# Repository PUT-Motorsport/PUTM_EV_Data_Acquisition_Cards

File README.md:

# PUTM_EV_Data_Acquisition_Cards
Project to read data from sensors and transmit it via CAN bus.

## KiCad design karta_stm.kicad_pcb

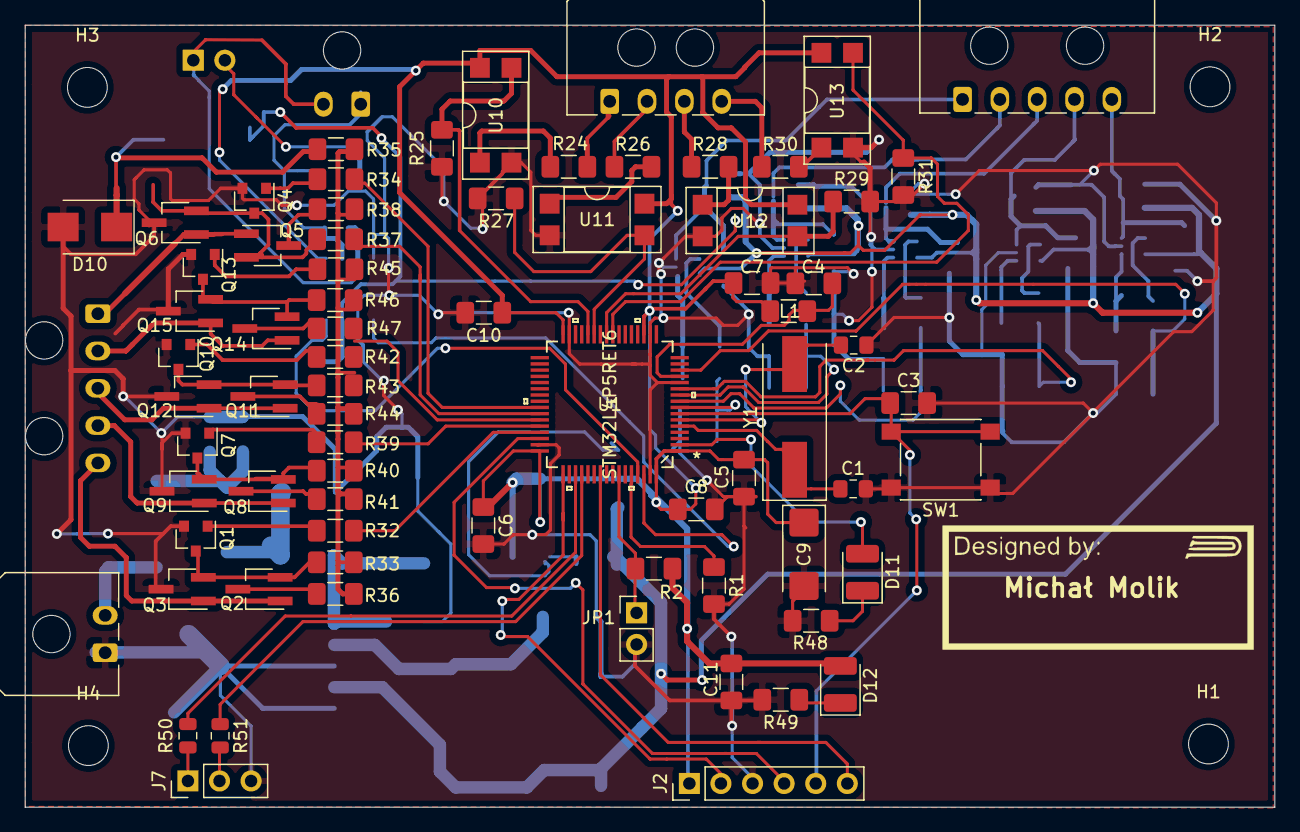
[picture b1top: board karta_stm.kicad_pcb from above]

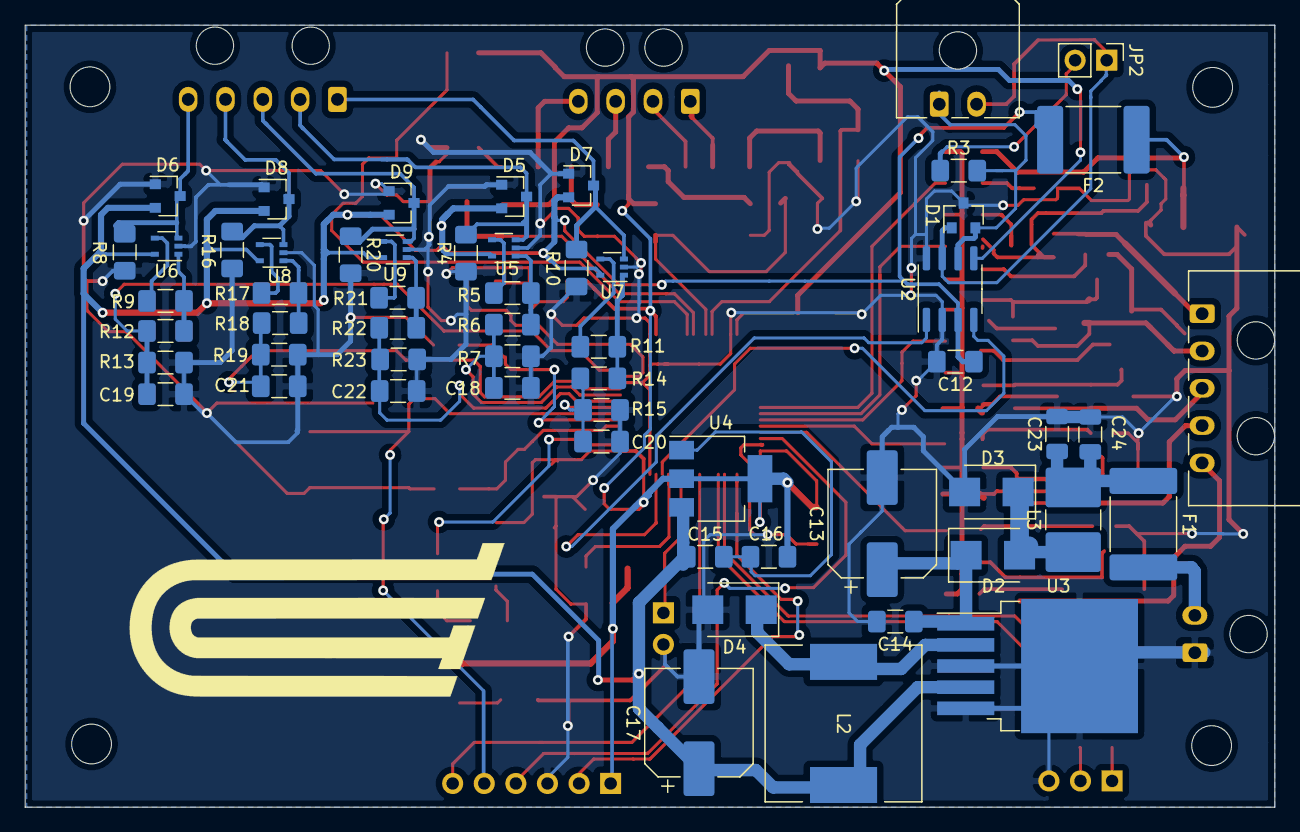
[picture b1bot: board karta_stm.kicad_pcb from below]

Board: 2 copper layers, 100.5 x 62.9 mm, 135 parts (58 on the bottom side), 89 nets.

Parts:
C1, C2: 20pF; C_0805_2012Metric_Pad1.15x1.40mm_HandSolder
C3, C18, C19, C20, C21, C22: 0.1uF; C_1206_3216Metric_Pad1.42x1.75mm_HandSolder
C4, C5, C6, C7, C8, C12, C14, C15, C16: 100nF; C_1206_3216Metric_Pad1.42x1.75mm_HandSolder
C9: 4,7uF; CP_EIA-6032-15_Kemet-U_Pad2.25x2.35mm_HandSolder
C10: 10nF; C_1206_3216Metric_Pad1.42x1.75mm_HandSolder
C11: 1uF; C_1206_3216Metric_Pad1.42x1.75mm_HandSolder
C13: 100uF; CP_Elec_8x10.5
C17: 220uF; CP_Elec_8x10.5
C23, C24: C; C_1206_3216Metric
D1: PESD2CAN,215; SOT-23
D2: SM6T30A; D_SMB
D3: D_Schottky; D_SMB
D4: 1N5824; D_SMB
D5, D6, D7, D8, D9: BAT54S; SOT-23
D10: SM6T6V8A; D_SMB
D11, D12: D; D_1210_3225Metric_Pad1.42x2.65mm_HandSolder
F1: 200mA; Fuse_2920_7451Metric_Pad2.10x5.45mm_HandSolder
F2: 100mA; Fuse_2920_7451Metric_Pad2.10x5.45mm_HandSolder
H1, H2, H3, H4: MountingHole; MountingHole_3.2mm_M3
J1, J4: Conn_01x02_Female; Molex_Micro-Fit_3.0_43650-0200_1x02_P3.00mm_Horizontal
J2: Conn_01x06_Male; PinHeader_1x06_P2.54mm_Vertical
J3, J5: Conn_01x05_Female; Molex_Micro-Fit_3.0_43650-0500_1x05_P3.00mm_Horizontal
J6: Conn_01x04_Female; Molex_Micro-Fit_3.0_43650-0400_1x04_P3.00mm_Horizontal
J7: Conn_01x03_Male; PinHeader_1x03_P2.54mm_Vertical
JP1, JP2: Jumper_2_Bridged; PinHeader_1x02_P2.54mm_Vertical
L1: L; L_1206_3216Metric_Pad1.42x1.75mm_HandSolder
L2: 33uH; L_12x12mm_H8mm
L3: L; L_2816_7142Metric_Pad3.20x4.45mm_HandSolder
Q1, Q4, Q7, Q10, Q13: BC817; SOT-23
Q2, Q5, Q8, Q11, Q14: Q_PMOS_DGS; SOT-23W_Handsoldering
Q3, Q6, Q9, Q12, Q15: Q_NMOS_DGS; SOT-23W_Handsoldering
R1: 0R; R_1206_3216Metric_Pad1.42x1.75mm_HandSolder
R2, R4, R8, R10, R16, R20: 10k Ohm; R_1206_3216Metric_Pad1.42x1.75mm_HandSolder
R3: 120 Ohm; R_1206_3216Metric_Pad1.42x1.75mm_HandSolder
R5, R9, R11, R17, R21: 11k; R_1206_3216Metric_Pad1.42x1.75mm_HandSolder
R6, R12, R14, R18, R22: 5.1k; R_1206_3216Metric_Pad1.42x1.75mm_HandSolder
R7, R13, R15, R19, R23, R24, R26, R28, R30, R33, R35, R36, R37, R38, R40, R43, R44, R46, R47: 10k; R_1206_3216Metric_Pad1.42x1.75mm_HandSolder
R25, R27, R29, R31: R; R_1206_3216Metric_Pad1.42x1.75mm_HandSolder
R32, R34, R39, R42, R45: 100R; R_1206_3216Metric_Pad1.42x1.75mm_HandSolder
R41: 100k; R_1206_3216Metric_Pad1.42x1.75mm_HandSolder
R48, R49: 1kOhm; R_1206_3216Metric_Pad1.42x1.75mm_HandSolder
R50, R51: R; R_0805_2012Metric
SW1: SW_Push; SW_Push_1P1T_NO_6x6mm_H9.5mm
U1: STM32L4P5RET6
U2: MCP2562-H-SN; SOIC-8_3.9x4.9mm_P1.27mm
U3: LM2596S-5; TO-263-5_TabPin3
U4: LD1117S33TR_SOT223; SOT-223-3_TabPin2
U5, U6, U7, U8, U9: MCP6001x-LT; SOT-353_SC-70-5
U10, U11, U12, U13: EL817; DIP-4_W7.62mm_SMDSocket_SmallPads
Y1: 16MHz; Crystal_SMD_HC49-SD

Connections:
+3V3: C5.1, C6.1, C7.1, C8.1, C9.1, C10.1, C11.1, C16.1, D12.2, J2.1, L1.1, R2.1, U1.1, U1.19, U1.32, U1.48, U1.64, U2.5, U4.2, U10.4, U11.4, U12.4, U13.4
+5V: C12.1, C15.1, C17.1, D5.2, D6.2, D7.2, D8.2, D9.2, F2.2, L2.1, U2.3, U3.4, U4.3, U5.5, U6.5, U7.5, U8.5, U9.5
+5VD: R33.1, R35.1, R36.1, R37.1, R38.1, R40.1, R41.1, R43.1, R44.1, R46.1, R47.1
+BATT: F1.2, J4.2
ADC_0: C19.1, R12.2, R13.1, U1.14
ADC_1: C21.1, R18.2, R19.1, U1.11
ADC_2: C22.1, R22.2, R23.1, U1.9
ADC_3: C18.1, R6.2, R7.1, U1.10
ADC_4: C20.1, R14.2, R15.1, U1.8
ADC_IN0: D6.3, J5.5, R8.1, U6.3
ADC_IN1: D8.3, J5.4, R16.1, U8.3
ADC_IN2: D9.3, J5.3, R20.1, U9.3
ADC_IN3: D5.3, J5.2, R4.1, U5.3
ADC_IN4: D7.3, J5.1, R10.1, U7.3
CAN_H: D1.1, J1.2, JP2.1, U2.7
CAN_L: D1.2, J1.1, R3.2, U2.6
CAN_RX: U1.61, U2.4
CAN_TX: U1.62, U2.1
DIODE_0: D11.2, U1.2
GND: C1.2, C2.1, C3.2, C4.2, C5.2, C6.2, C7.2, C8.2, C9.2, C10.2, C11.2, C12.2, C13.2, C14.2, C17.2, C18.2, C19.2, C20.2, C21.2, C22.2, C23.2, C24.2, D1.3, D2.2, D4.2, D5.1, D6.1, D7.1, D8.1, D9.1, D10.2, J2.3, J4.1, J7.3, JP1.2, Q1.2, Q3.3, Q4.2, Q6.3, Q7.2, Q9.3, Q10.2, Q12.3, Q13.2, Q15.3, R1.2, R4.2, R7.2, R8.2, R10.2, R13.2, R15.2, R16.2, R19.2, R20.2, R23.2, R25.2, R27.2, R29.2, R31.2, R48.2, R49.2, SW1.1, U1.12, U1.18, U1.31, U1.47, U1.63, U2.2, U2.8, U3.3, U3.5, U5.2, U6.2, U7.2, U8.2, U9.2, U10.2, U11.2, U12.2, U13.2
INPUT_0: R25.1, U1.28, U10.3
INPUT_1: R27.1, U1.27, U11.3
INPUT_2: R29.1, U1.25, U12.3
INPUT_3: R31.1, U1.24, U13.3
IN_0: J6.1, R24.1
IN_1: J6.2, R26.1
IN_2: J6.3, R28.1
IN_3: J6.4, R30.1
NRST: C3.1, J2.5, SW1.2, U1.7
unnamed: C4.1, L1.2, U1.13
unnamed: C13.1, C14.1, D3.1, U3.1
unnamed: C15.2, C16.2, U4.1
unnamed: C23.1, C24.1, F1.1, L3.2
unnamed: D2.1, D3.2, L3.1
unnamed: D4.1, L2.2, U3.2
unnamed: D10.1, F2.1, R35.2
unnamed: D11.1, R48.1
unnamed: D12.1, R49.1
unnamed: J7.1, R50.2
unnamed: J7.2, R51.2
unnamed: JP2.2, R3.1
unnamed: Q1.1, R32.1
unnamed: Q1.3, Q2.2, Q3.2, R33.2
unnamed: Q2.3, R36.2
unnamed: Q4.1, R34.1
unnamed: Q4.3, Q5.2, Q6.2, R37.2
unnamed: Q5.3, R38.2
unnamed: Q7.1, R39.2
unnamed: Q7.3, Q8.2, Q9.2, R40.2
unnamed: Q8.3, R41.2
unnamed: Q10.1, R42.1
unnamed: Q10.3, Q11.2, Q12.2, R43.2
unnamed: Q11.3, R44.2
unnamed: Q13.1, R45.1
unnamed: Q13.3, Q14.2, Q15.2, R46.2
unnamed: Q14.3, R47.2
unnamed: R1.1, U1.60
unnamed: R5.1, R6.1, U5.1
unnamed: R5.2, U5.4
unnamed: R9.2, U6.4
unnamed: R11.1, R14.1, U7.1
unnamed: R11.2, U7.4
unnamed: R9.1, R12.1, U6.1
unnamed: R17.1, R18.1, U8.1
unnamed: R17.2, U8.4
unnamed: R21.1, R22.1, U9.1
unnamed: R21.2, U9.4
unnamed: R24.2, U10.1
unnamed: R26.2, U11.1
unnamed: R28.2, U12.1
unnamed: R30.2, U13.1
OSC_IN: C1.1, U1.5, Y1.1
OSC_OUT: C2.2, U1.6, Y1.2
OUTPUT_0: R32.2, U1.45
OUTPUT_1: R39.1, U1.44
OUTPUT_2: R42.2, U1.43
OUTPUT_3: R45.2, U1.42
OUTPUT_4: R34.2, U1.41
OUT_0: J3.5, Q2.1, Q3.1
OUT_1: J3.4, Q8.1, Q9.1
OUT_2: J3.3, Q11.1, Q12.1
OUT_3: J3.2, Q14.1, Q15.1
OUT_4: J3.1, Q5.1, Q6.1
SWDCLK: J2.2, U1.49
SWDIO: J2.4, U1.46
SWO: J2.6, U1.55
UART_RX: R51.1, U1.52
UART_TX: R50.1, U1.51
zwora: JP1.1, R2.2, U1.58

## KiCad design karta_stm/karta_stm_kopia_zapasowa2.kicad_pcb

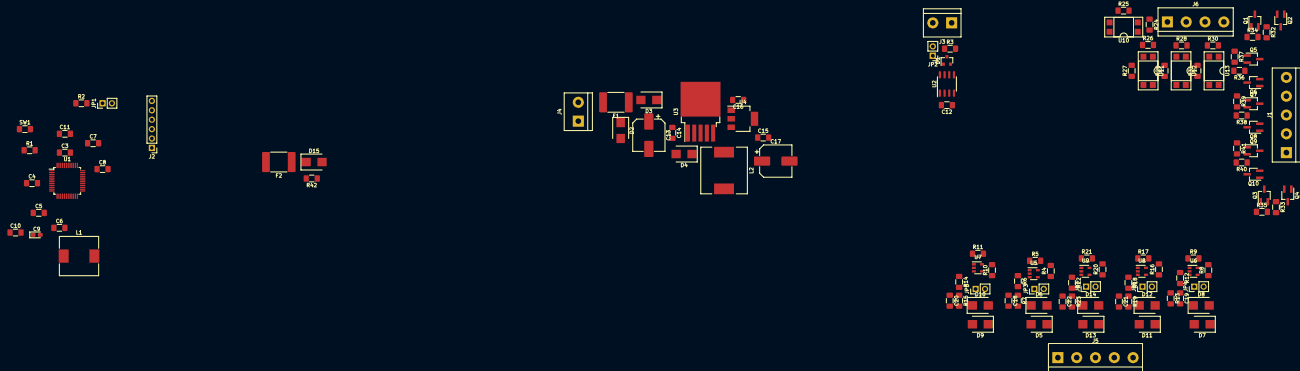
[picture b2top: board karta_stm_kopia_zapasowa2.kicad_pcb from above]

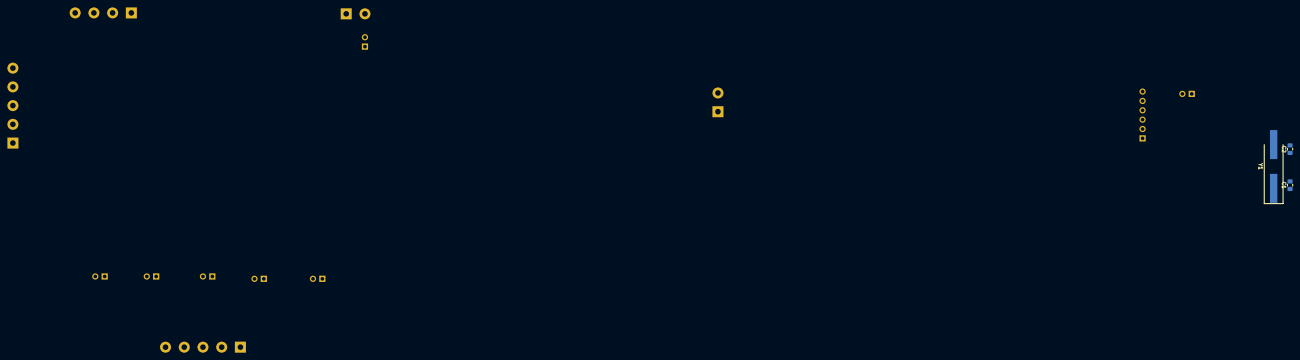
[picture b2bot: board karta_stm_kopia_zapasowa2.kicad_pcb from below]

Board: 2 copper layers, 121 parts (3 on the bottom side), 80 nets, no tracks yet.

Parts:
C1, C2: 20pF; C_0805_2012Metric_Pad1.15x1.40mm_HandSolder
C3, C18, C19, C20, C21, C22: C; C_1206_3216Metric_Pad1.42x1.75mm_HandSolder
C4, C5, C6, C7, C8, C12, C14, C15, C16: 100nF; C_1206_3216Metric_Pad1.42x1.75mm_HandSolder
C9: 4,7uF; CP_EIA-2012-12_Kemet-R_Pad1.30x1.05mm_HandSolder
C10: 10nF; C_1206_3216Metric_Pad1.42x1.75mm_HandSolder
C11: 1uF; C_1206_3216Metric_Pad1.42x1.75mm_HandSolder
C13: 100uF; CP_Elec_8x10.5
C17: 220uF; CP_Elec_8x10.5
D1: PESD2CAN,215; SOT-23
D2: SM6T30A; D_SMB
D3, D5, D6, D7, D8, D9, D10, D11, D12, D13, D14: D_Schottky; D_SMB
D4: 1N5824; D_SMB
D15: SM6T6V8A; D_SMB
F1: F; Fuse_2920_7451Metric_Pad2.10x5.45mm_HandSolder
F2: Fuse; Fuse_2920_7451Metric_Pad2.10x5.45mm_HandSolder
J1, J5: Screw_Terminal_01x05; TerminalBlock_bornier-5_P5.08mm
J2: Conn_01x06_Male; PinHeader_1x06_P2.54mm_Vertical
J3, J4: Screw_Terminal_01x02; TerminalBlock_bornier-2_P5.08mm
J6: Screw_Terminal_01x04; TerminalBlock_bornier-4_P5.08mm
JP1, JP2, JP3, JP4, JP5, JP6, JP7: Jumper_2_Bridged; PinHeader_1x02_P2.54mm_Vertical
L1: L; L_10.4x10.4_H4.8
L2: 33uH; L_12x12mm_H8mm
Q1, Q3, Q5, Q7, Q9: Q_PMOS_DGS; SOT-23W_Handsoldering
Q2, Q4, Q6, Q8, Q10: Q_NMOS_DGS; SOT-23W_Handsoldering
R1, R5, R6, R7, R9, R11, R12, R13, R14, R15, R17, R18, R19, R21, R22, R23, R24, R25, R26, R27, R28, R29, R30, R31, R32, R33, R34, R35, R36, R37, R38, R39, R40, R41, R42: R; R_1206_3216Metric_Pad1.42x1.75mm_HandSolder
R2, R4, R8, R10, R16, R20: 10k Ohm; R_1206_3216Metric_Pad1.42x1.75mm_HandSolder
R3: 120 Ohm; R_1206_3216Metric_Pad1.42x1.75mm_HandSolder
SW1: SW_Push; R_1206_3216Metric_Pad1.42x1.75mm_HandSolder
U1: STM32F103C8Tx; LQFP-48_7x7mm_P0.5mm
U2: MCP2562-H-SN; SOIC-8_3.9x4.9mm_P1.27mm
U3: LM2596S-5; TO-263-5_TabPin3
U4: LD1117S33TR_SOT223; SOT-223-3_TabPin2
U5, U6, U7, U8, U9: MCP6001R; SOT-23-5
U10, U11, U12, U13: EL817; DIP-4_W7.62mm_SMDSocket_SmallPads
Y1: 16MHz; Crystal_SMD_HC49-SD_HandSoldering

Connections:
+3V3: C5.1, C6.1, C7.1, C8.1, C9.1, C10.1, C11.1, C16.1, J2.1, L1.1, R2.1, U1.1, U1.24, U1.36, U1.48, U2.5, U4.2, U10.4, U11.4, U12.4, U13.4
+5V: C12.1, C15.1, C17.1, D5.1, D7.1, D9.1, D11.1, D13.1, F2.2, L2.1, U2.3, U3.4, U4.3, U5.2, U6.2, U7.2, U8.2, U9.2
+5VD: R34.1, R35.1, R37.1, R39.1, R41.1, R42.1
+BATT: F1.2, J4.2
ADC_0: C19.1, R12.2, R13.1, U1.10
ADC_1: C21.1, R18.2, R19.1, U1.11
ADC_2: C22.1, R22.2, R23.1, U1.12
ADC_3: C18.1, R6.2, R7.1, U1.13
ADC_4: C20.1, R14.2, R15.1, U1.14
ADC_IN0: D7.2, D8.1, J5.5, JP4.1, U6.3
ADC_IN1: D11.2, D12.1, J5.4, JP6.1, U8.3
ADC_IN2: D13.2, D14.1, J5.3, JP7.1, U9.3
ADC_IN3: D5.2, D6.1, J5.2, JP3.1, U5.3
ADC_IN4: D9.2, D10.1, J5.1, JP5.1, U7.3
CAN_H: D1.1, J3.2, JP2.1, U2.7
CAN_L: D1.2, J3.1, R3.2, U2.6
CAN_RX: U1.32, U2.4
CAN_TX: U1.33, U2.1
GND: C1.2, C2.1, C3.2, C4.2, C5.2, C6.2, C7.2, C8.2, C9.2, C10.2, C11.2, C12.2, C13.2, C14.2, C15.2, C16.2, C17.2, C18.2, C19.2, C20.2, C21.2, C22.2, D1.3, D2.2, D4.2, D6.2, D8.2, D10.2, D12.2, D14.2, D15.2, J2.3, J4.1, JP1.2, Q2.3, Q4.3, Q6.3, Q8.3, Q10.3, R1.2, R4.2, R7.2, R8.2, R10.2, R13.2, R15.2, R16.2, R19.2, R20.2, R23.2, R25.2, R27.2, R29.2, R31.2, SW1.1, U1.8, U1.23, U1.35, U1.47, U2.2, U2.8, U3.3, U3.5, U4.1, U5.5, U6.5, U7.5, U8.5, U9.5, U10.2, U11.2, U12.2, U13.2
INPUT_0: R25.1, U1.18, U10.3
INPUT_1: R27.1, U1.19, U11.3
INPUT_2: R29.1, U1.20, U12.3
INPUT_3: R31.1, U1.40, U13.3
IN_0: J6.1, R24.1
IN_1: J6.2, R26.1
IN_2: J6.3, R28.1
IN_3: J6.4, R30.1
NRST: C3.1, J2.5, SW1.2, U1.7
unnamed: C1.1, U1.5, Y1.1
unnamed: C2.2, U1.6, Y1.2
unnamed: C4.1, L1.2, U1.9
unnamed: C13.1, C14.1, D3.1, U3.1
unnamed: D2.1, D3.2, F1.1
unnamed: D4.1, L2.2, U3.2
unnamed: D15.1, F2.1, R42.2
unnamed: JP2.2, R3.1
unnamed: JP3.2, R4.1
unnamed: JP4.2, R8.1
unnamed: JP5.2, R10.1
unnamed: JP6.2, R16.1
unnamed: JP7.2, R20.1
unnamed: Q1.1, R34.2
unnamed: Q1.2, Q2.2, R32.1
unnamed: Q3.1, R35.2
unnamed: Q3.2, Q4.2, R33.1
unnamed: Q5.1, R37.2
unnamed: Q5.2, Q6.2, R36.1
unnamed: Q7.1, R39.2
unnamed: Q7.2, Q8.2, R38.1
unnamed: Q9.1, R41.2
unnamed: Q9.2, Q10.2, R40.1
unnamed: R1.1, U1.44
unnamed: R5.1, R6.1, U5.1
unnamed: R5.2, U5.4
unnamed: R9.2, U6.4
unnamed: R11.1, R14.1, U7.1
unnamed: R11.2, U7.4
unnamed: R9.1, R12.1, U6.1
unnamed: R17.1, R18.1, U8.1
unnamed: R17.2, U8.4
unnamed: R21.1, R22.1, U9.1
unnamed: R21.2, U9.4
unnamed: R24.2, U10.1
unnamed: R26.2, U11.1
unnamed: R28.2, U12.1
unnamed: R30.2, U13.1
OUTPUT_0: R32.2, U1.16
OUTPUT_1: R36.2, U1.17
OUTPUT_2: R38.2, U1.29
OUTPUT_3: R40.2, U1.30
OUTPUT_4: R33.2, U1.31
OUT_0: J1.5, Q1.3, Q2.1
OUT_1: J1.4, Q5.3, Q6.1
OUT_2: J1.3, Q7.3, Q8.1
OUT_3: J1.2, Q9.3, Q10.1
OUT_4: J1.1, Q3.3, Q4.1
SWDCLK: J2.2, U1.37
SWDIO: J2.4, U1.34
SWO: J2.6, U1.39
zwora: JP1.1, R2.2, U1.28

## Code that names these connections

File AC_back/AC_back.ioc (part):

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Mcu.UserName=STM32L4P5RETx
PH0-OSC_IN\ (PH0).Signal=RCC_OSC_IN
PC10.Signal=UART4_TX
PA0.GPIO_Label=ADC_0
PC0.GPIOParameters=GPIO_Label
PA9.GPIOParameters=GPIO_Label
PA11.GPIOParameters=GPIO_Label
PC0.GPIO_Label=ADC_4
PB6.GPIO_Label=JUMPER
PC13.GPIO_Label=DIODE_0
RCC.SYSCLKSource=RCC_SYSCLKSOURCE_PLLCLK
PA12.Signal=GPIO_Output
PC1.GPIOParameters=GPIO_Label
PB6.Signal=GPIO_Input
PC3.Signal=ADCx_IN4
PA8.GPIOParameters=GPIO_Label
PH1-OSC_OUT\ (PH1).Mode=HSE-External-Oscillator
RCC.HSE_VALUE=16000000
PB2.Signal=GPXTI2
PC4.GPIO_Label=RTD_input
PA10.GPIO_Label=D_OUTPUT_2
PC13.GPIO_PuPd=GPIO_PULLDOWN
PA8.Signal=GPIO_Output
PB6.GPIOParameters=GPIO_Label
PA0.Signal=ADCx_IN5
PB9.Signal=CAN1_TX
Mcu.Package=LQFP64
PB1.Signal=S_TIM3_CH4
PA10.Signal=GPIO_Output
PC11.Mode=Asynchronous
PH0-OSC_IN\ (PH0).Mode=HSE-External-Oscillator
PC2.GPIO_Label=ADC_2
PC4.GPIOParameters=GPIO_Label
PA9.GPIO_Label=D_OUTPUT_3
PC13.Signal=GPIO_Output
PC11.Signal=UART4_RX
PC2.Signal=ADCx_IN3
PC4.Signal=GPXTI4
PC10.Mode=Asynchronous
PA11.GPIO_Label=D_OUTPUT_1
PC0.Signal=ADCx_IN1
PH1-OSC_OUT\ (PH1).Signal=RCC_OSC_OUT
PC3.GPIOParameters=GPIO_Label
PA8.GPIO_Label=D_OUTPUT_4
PB9.Mode=CAN_Activate
PB2.GPIOParameters=GPIO_Label
PA9.Signal=GPIO_Output
board=custom
PC13.GPIOParameters=GPIO_PuPd,GPIO_Label
PC2.GPIOParameters=GPIO_Label
PC1.GPIO_Label=ADC_3
PA10.GPIOParameters=GPIO_Label
Mcu.Name=STM32L4P5R(G-E)Tx
RCC.SYSCLKFreq_VALUE=72000000
PA11.Signal=GPIO_Output
PB2.GPIO_Label=BRK_input
PA0.GPIOParameters=GPIO_Label
PB8.Mode=CAN_Activate
PB8.Signal=CAN1_RX
PC3.GPIO_Label=ADC_1
PB0.Signal=S_TIM3_CH3
PC1.Signal=ADCx_IN2

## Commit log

2021-03-15 Usart and speed
    USART and rotary speed
2021-04-17 remove .cproject
2021-04-17 remove trash
2021-05-13 Commit change
2021-05-13 remove files
2021-05-24 config
2021-05-30 added functions
    -CAN communication
    -UART communication
    -speed meansuring
    -DMA and ADC
    -timer IT handler
2021-05-30 remove garbage
2021-06-04 hard
2021-06-04 Remove
2021-06-04 changed
2021-06-06 Update pcb
2021-06-14 chng
2021-06-15 add 100hz can
2021-06-16 CAN handlers
2021-06-16 Remove DEbug, Driver etc
2021-06-20 First run
2021-06-27 First test
    -RTDS
    -BRK signal
2021-06-27 500kbit/s
2021-07-09 Wheel speed
2021-07-09 Data Acquisition Card Back
2021-07-09 remove AC folder
2021-07-18 brk_light
2021-08-06 AC ready
2021-08-06 a few changes to test
2021-08-31 1mb/s
2021-09-25 without_can
2021-09-25 with_can + zip

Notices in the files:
parts and their libraries:
Copyright 2016 Accelerated Designs. All rights reserved.
